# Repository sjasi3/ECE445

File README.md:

READ ME File so repo isnt empty

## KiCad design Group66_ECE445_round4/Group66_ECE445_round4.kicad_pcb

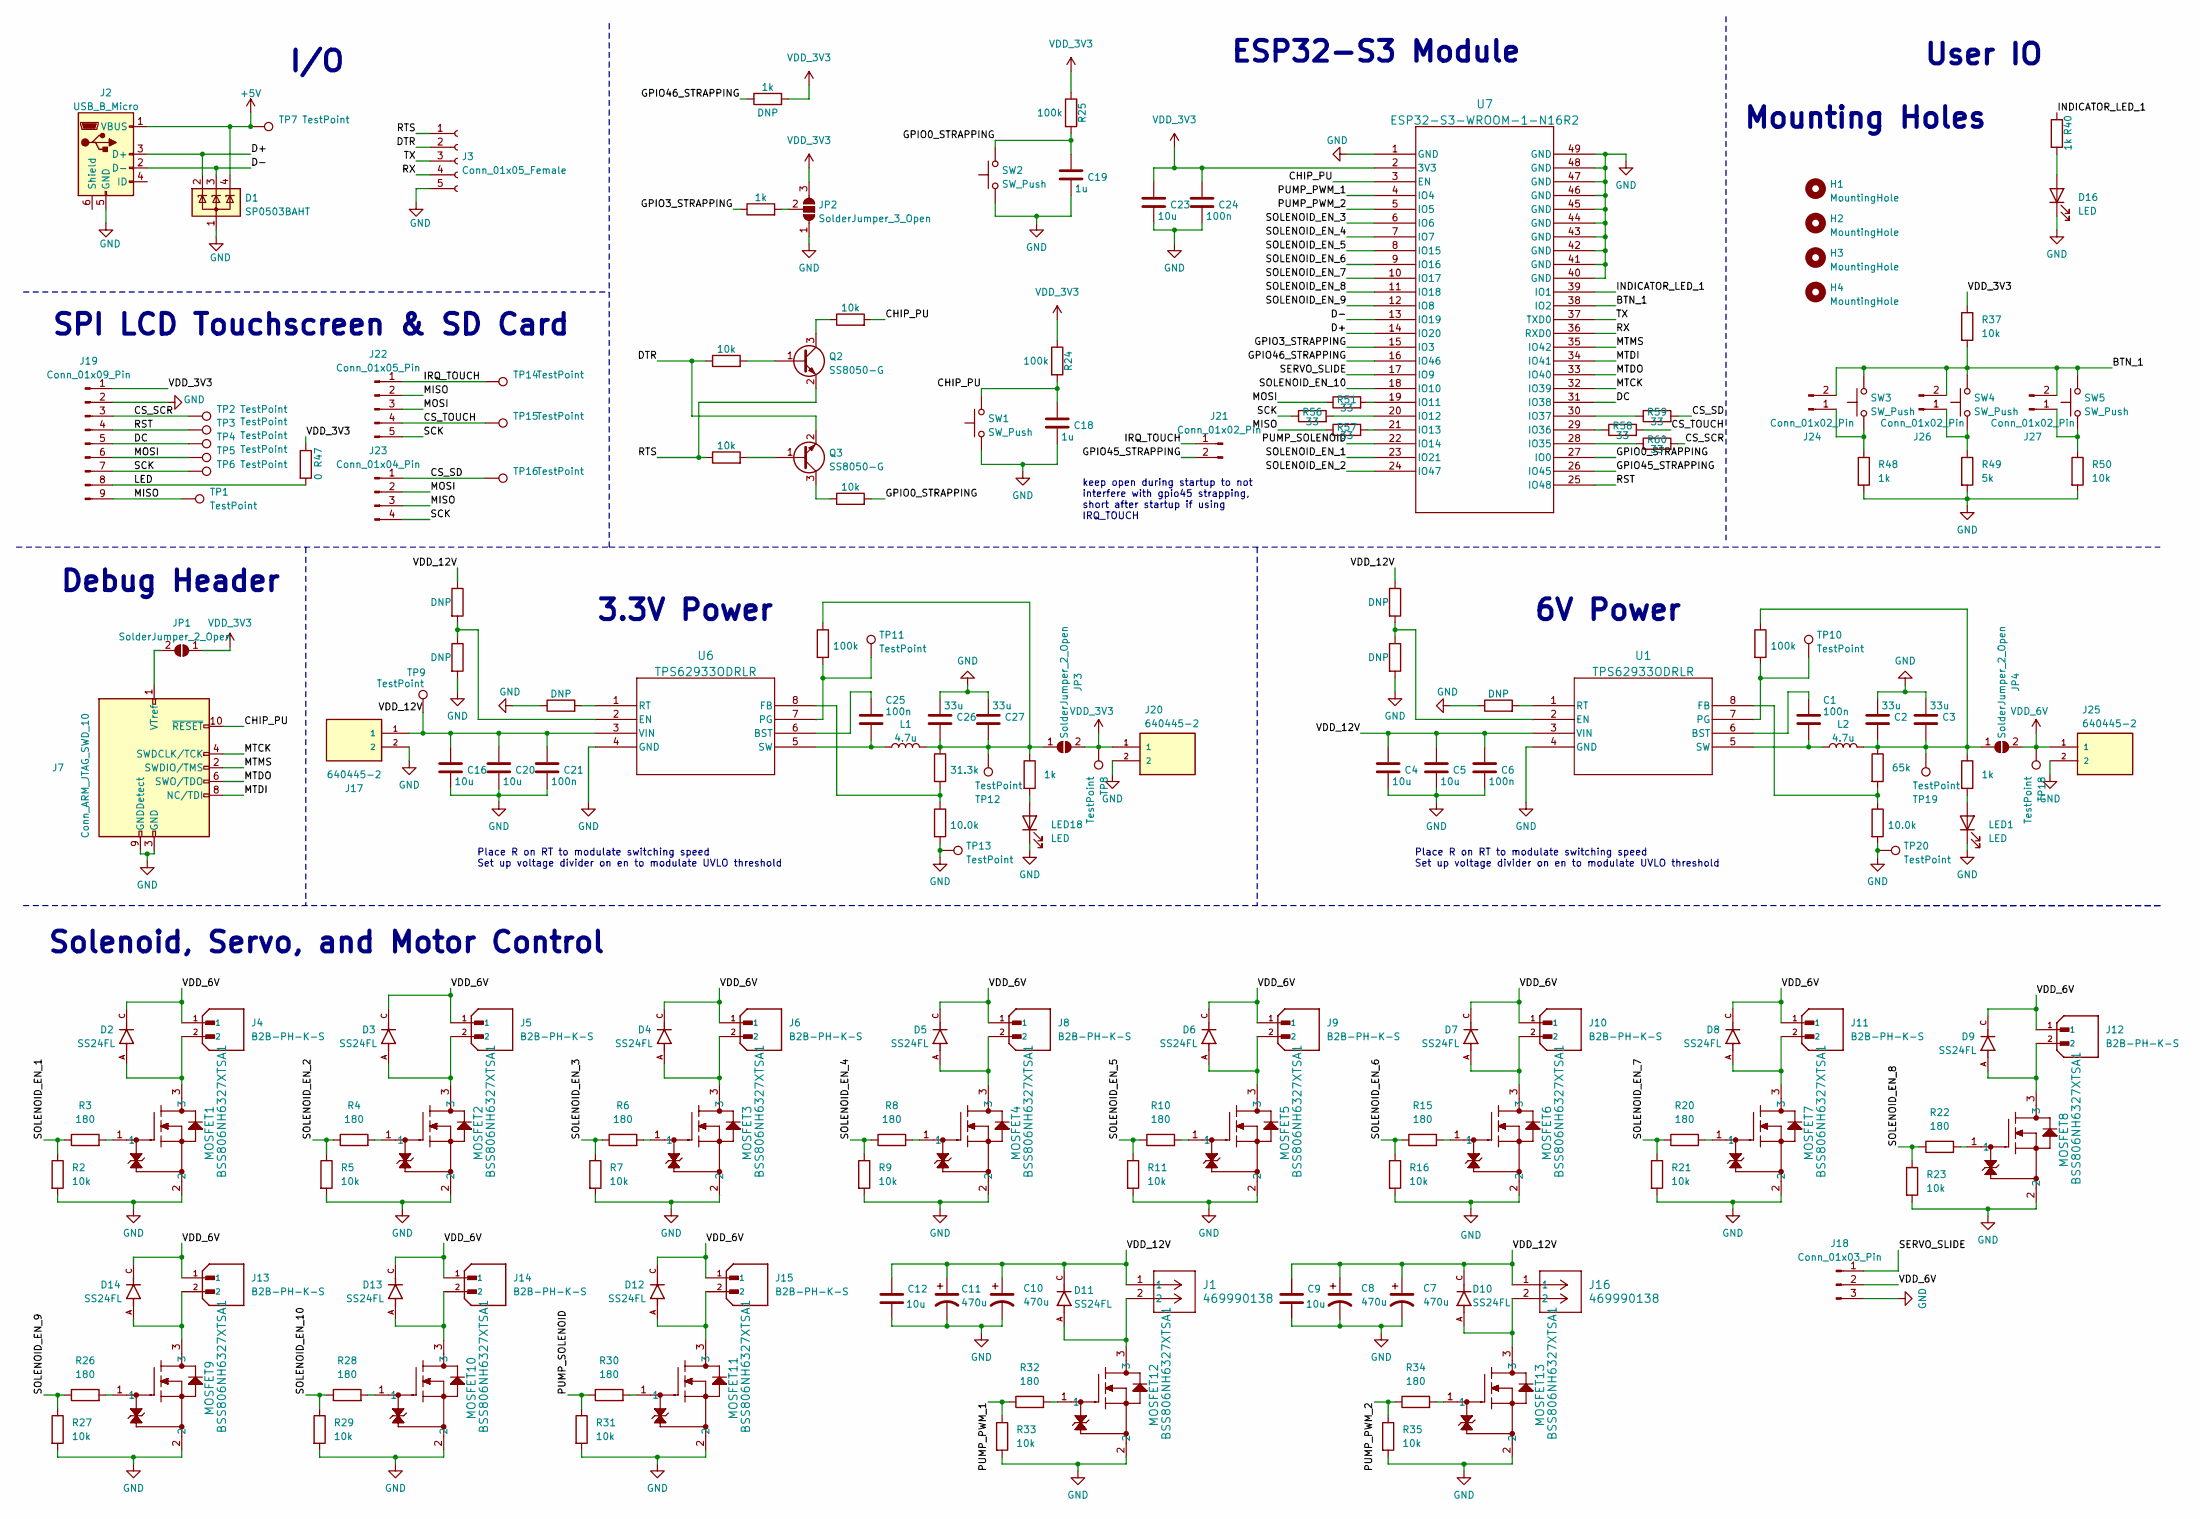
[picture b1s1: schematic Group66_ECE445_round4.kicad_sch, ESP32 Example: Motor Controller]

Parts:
C1, C6, C21, C24, C25: 100n; C_0805_2012Metric_Pad1.18x1.45mm_HandSolder
C2, C3, C26, C27: 33u; C_0805_2012Metric_Pad1.18x1.45mm_HandSolder
C4, C5, C9, C12, C16, C20, C23: 10u; C_0805_2012Metric_Pad1.18x1.45mm_HandSolder
C7, C8, C10, C11: 470u; CP_Radial_D8.0mm_P5.00mm
C18, C19: 1u; C_0805_2012Metric_Pad1.18x1.45mm_HandSolder
D1: SP0503BAHT; SOT-143
D2, D3, D4, D5, D6, D7, D8, D9, D10, D11, D12, D13, D14: SS24FL; SODFL3617X108N; PARTREV A
D16: LED; LED_0805_2012Metric_Pad1.15x1.40mm_HandSolder
H1, H2, H3, H4: MountingHole; MountingHole_3.2mm_M3
J1, J16: 469990138; CONN_SD-5566-002_02_MOL
J2: USB_B_Micro; USB_Micro-B_Amphenol_10118194_Horizontal
J3: Conn_01x05_Female; PinHeader_1x05_P2.54mm_Vertical
J4, J5, J6, J8, J9, J10, J11, J12, J13, J14, J15: B2B-PH-K-S; JST_B2B-PH-K-S; PARTREV N/A
J7: Conn_ARM_JTAG_SWD_10; IDC-Header_2x05_P2.54mm_Vertical
J17, J20, J25: 640445-2; TE_640445-2; PARTREV R
J18: Conn_01x03_Pin; PinHeader_1x03_P2.54mm_Vertical
J19: Conn_01x09_Pin; PinHeader_1x09_P2.54mm_Vertical
J21, J24, J26, J27: Conn_01x02_Pin; PinHeader_1x02_P2.54mm_Vertical
J22: Conn_01x05_Pin; PinHeader_1x05_P2.54mm_Vertical
J23: Conn_01x04_Pin; PinHeader_1x04_P2.54mm_Vertical
JP1, JP3, JP4: SolderJumper_2_Open; SolderJumper-2_P1.3mm_Open_TrianglePad1.0x1.5mm
JP2: SolderJumper_3_Open; SolderJumper-3_P2.0mm_Open_TrianglePad1.0x1.5mm
L1, L2: 4.7u; L_Taiyo-Yuden_NR-60xx
LED1, LED18: LED; LED_0805_2012Metric_Pad1.15x1.40mm_HandSolder
MOSFET1, MOSFET2, MOSFET3, MOSFET4, MOSFET5, MOSFET6, MOSFET7, MOSFET8, MOSFET9, MOSFET10, MOSFET11, MOSFET12, MOSFET13: BSS806NH6327XTSA1; SOT23_BSS806NH6327XTSA1_INF
Q2, Q3: SS8050-G; SOT-23
R1, R38, R41, R42, R43, R52: DNP; R_0805_2012Metric_Pad1.20x1.40mm_HandSolder
R2, R5, R7, R9, R11, R13, R14, R16, R18, R19, R21, R23, R27, R29, R31, R33, R35, R37, R50: 10k; R_0805_2012Metric_Pad1.20x1.40mm_HandSolder
R3, R4, R6, R8, R10, R15, R20, R22, R26, R28, R30, R32, R34: 180; R_0805_2012Metric_Pad1.20x1.40mm_HandSolder
R12, R17, R40, R46, R48, R54: 1k; R_0805_2012Metric_Pad1.20x1.40mm_HandSolder
R24, R25, R36, R39: 100k; R_0805_2012Metric_Pad1.20x1.40mm_HandSolder
R44: 31.3k; R_0805_2012Metric_Pad1.20x1.40mm_HandSolder
R45, R55: 10.0k; R_0805_2012Metric_Pad1.20x1.40mm_HandSolder
R47: 0; R_0805_2012Metric_Pad1.20x1.40mm_HandSolder
R49: 5k; R_0805_2012Metric_Pad1.20x1.40mm_HandSolder
R51, R56, R57, R58, R59, R60: 33; R_0805_2012Metric_Pad1.20x1.40mm_HandSolder
R53: 65k; R_0805_2012Metric_Pad1.20x1.40mm_HandSolder
SW1, SW2, SW3, SW4, SW5: SW_Push; SW_SPST_B3S-1000
TP1, TP2, TP3, TP4, TP5, TP6, TP7, TP8, TP9, TP10, TP11, TP12, TP13, TP14, TP15, TP16, TP18, TP19, TP20: TestPoint; TestPoint_Pad_D1.5mm
U1, U6: TPS62933ODRLR; SOT5X3-8_DRL_TEX
U7: ESP32-S3-WROOM-1-N16R2; ESP32-S3-WROOM-1_EXP

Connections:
+5V: D1.4 (K), J2.1 (VBUS), TP7.1
/BTN_1: J24.2, J26.2, J27.2, R37.2, SW3.2, SW4.2, SW5.2, U7.38 (IO2)
/CHIP_PU: C18.1, J7.10 (~RESET), R18.2, R24.2, SW1.2, U7.3 (EN)
/CS_SCR: J19.3, R60.2, TP2.1
/CS_SD: J23.1, R59.2, TP16.1
/CS_TOUCH: J22.4, R58.2, TP15.1
/D+: D1.2 (K), J2.3 (D+), U7.14 (IO20)
/D-: D1.3 (K), J2.2 (D-), U7.13 (IO19)
/DC: J19.5, TP4.1, U7.31 (IO38)
/DTR: J3.2, Q3.2 (E), R13.1
/GPIO0_STRAPPING: C19.1, R19.2, R25.2, SW2.2, U7.27 (IO0)
/GPIO3_STRAPPING: R17.1, U7.15 (IO3)
/GPIO45_STRAPPING: J21.2, U7.26 (IO45)
/GPIO46_STRAPPING: R12.1, U7.16 (IO46)
/INDICATOR_LED_1: R40.1, U7.39 (IO1)
/IRQ_TOUCH: J21.1, J22.1, TP14.1
/LED: J19.8, R47.2
/MISO: J19.9, J22.2, J23.3, R57.1, TP1.1
/MOSI: J19.6, J22.3, J23.2, R51.1, TP5.1
/MTCK: J7.4 (SWDCLK/TCK), U7.32 (IO39)
/MTDI: J7.8 (NC/TDI), U7.34 (IO41)
/MTDO: J7.6 (SWO/TDO), U7.33 (IO40)
/MTMS: J7.2 (SWDIO/TMS), U7.35 (IO42)
/PUMP_PWM_1: R32.1, R33.1, U7.4 (IO4)
/PUMP_PWM_2: R34.1, R35.1, U7.5 (IO5)
/PUMP_SOLENOID: R30.1, R31.1, U7.22 (IO14)
/RST: J19.4, TP3.1, U7.25 (IO48)
/RTS: J3.1, Q2.2 (E), R14.1
/RX: J3.4, U7.36 (RXD0)
/SCK: J19.7, J22.5, J23.4, R56.1, TP6.1
/SERVO_SLIDE: J18.1, U7.17 (IO9)
/SOLENOID_EN_1: R2.1, R3.1, U7.23 (IO21)
/SOLENOID_EN_2: R4.1, R5.1, U7.24 (IO47)
/SOLENOID_EN_3: R6.1, R7.1, U7.6 (IO6)
/SOLENOID_EN_4: R8.1, R9.1, U7.7 (IO7)
/SOLENOID_EN_5: R10.1, R11.1, U7.8 (IO15)
/SOLENOID_EN_6: R15.1, R16.1, U7.9 (IO16)
/SOLENOID_EN_7: R20.1, R21.1, U7.10 (IO17)
/SOLENOID_EN_8: R22.1, R23.1, U7.11 (IO18)
/SOLENOID_EN_9: R26.1, R27.1, U7.12 (IO8)
/SOLENOID_EN_10: R28.1, R29.1, U7.18 (IO10)
/TX: J3.3, U7.37 (TXD0)
/VDD_12V: C4.1, C5.1, C6.1, C7.1, C8.1, C9.1, C10.1, C11.1, C12.1, C16.1, C20.1, C21.1, D10.C, D11.C, J1.1, J16.1, J17.1, R1.1, R38.1, TP9.1, U1.3 (VIN), U6.3 (VIN)
GND: C2.2, C3.2, C4.2, C5.2, C6.2, C7.2, C8.2, C9.2, C10.2, C11.2, C12.2, C16.2, C18.2, C19.2, C20.2, C21.2, C23.2, C24.2, C26.2, C27.2, D1.1 (A), D16.1 (K), J2.5 (GND), J3.5, J7.3 (GND), J7.5 (GND), J7.9 (GNDDetect), J17.2, J18.3, J19.2, J20.2, J25.2, JP2.1 (A), LED1.1 (K), LED18.1 (K), MOSFET1.2, MOSFET2.2, MOSFET3.2, MOSFET4.2, MOSFET5.2, MOSFET6.2, MOSFET7.2, MOSFET8.2, MOSFET9.2, MOSFET10.2, MOSFET11.2, MOSFET12.2, MOSFET13.2, R2.2, R5.2, R7.2, R9.2, R11.2, R16.2, R21.2, R23.2, R27.2, R29.2, R31.2, R33.2, R35.2, R41.2, R42.2, R43.1, R45.2, R48.2, R49.2, R50.2, R52.1, R55.2, SW1.1, SW2.1, TP13.1, TP20.1, U1.4 (GND), U6.4 (GND), U7.1 (GND), U7.40 (GND), U7.41 (GND), U7.42 (GND), U7.43 (GND), U7.44 (GND), U7.45 (GND), U7.46 (GND), U7.47 (GND), U7.48 (GND), U7.49 (GND)
unnamed: D2.A, J4.2, MOSFET1.3
unnamed: D3.A, J5.2, MOSFET2.3
unnamed: D4.A, J6.2, MOSFET3.3
unnamed: D5.A, J8.2, MOSFET4.3
unnamed: D6.A, J9.2, MOSFET5.3
unnamed: D7.A, J10.2, MOSFET6.3
unnamed: D8.A, J11.2, MOSFET7.3
unnamed: D9.A, J12.2, MOSFET8.3
unnamed: D10.A, J16.2, MOSFET13.3
unnamed: D11.A, J1.2, MOSFET12.3
unnamed: D12.A, J15.2, MOSFET11.3
unnamed: D13.A, J14.2, MOSFET10.3
unnamed: D14.A, J13.2, MOSFET9.3
unnamed: D16.2 (A), R40.2
unnamed: J7.1 (VTref), JP1.2 (B)
unnamed: J24.1, R48.1, SW3.1
unnamed: J26.1, R49.1, SW4.1
unnamed: J27.1, R50.1, SW5.1
unnamed: JP2.2 (C), R17.2
unnamed: C26.1, C27.1, JP3.1 (A), L1.2, R36.1, R44.1, R46.1, TP12.1
unnamed: C2.1, C3.1, JP4.1 (A), L2.2, R39.1, R53.1, R54.1, TP19.1
unnamed: LED1.2 (A), R54.2
unnamed: LED18.2 (A), R46.2
unnamed: MOSFET1.1, R3.2
unnamed: MOSFET2.1, R4.2
unnamed: MOSFET3.1, R6.2
unnamed: MOSFET4.1, R8.2
unnamed: MOSFET5.1, R10.2
unnamed: MOSFET6.1, R15.2
unnamed: MOSFET7.1, R20.2
unnamed: MOSFET8.1, R22.2
unnamed: MOSFET9.1, R26.2
unnamed: MOSFET10.1, R28.2
unnamed: MOSFET11.1, R30.2
unnamed: MOSFET12.1, R32.2
unnamed: MOSFET13.1, R34.2
unnamed: Q2.1 (B), R13.2
unnamed: Q2.3 (C), R18.1
unnamed: Q3.1 (B), R14.2
unnamed: Q3.3 (C), R19.1
unnamed: C1.1, U1.6 (BST)
unnamed: R38.2, R41.1, U1.2 (EN)
unnamed: R53.2, R55.1, U1.8 (FB)
unnamed: R39.2, TP10.1, U1.7 (PG)
unnamed: R52.2, U1.1 (RT)
unnamed: C1.2, L2.1, U1.5 (SW)
unnamed: C25.1, U6.6 (BST)
unnamed: R1.2, R42.1, U6.2 (EN)
unnamed: R44.2, R45.1, U6.8 (FB)
unnamed: R36.2, TP11.1, U6.7 (PG)
unnamed: R43.2, U6.1 (RT)
unnamed: C25.2, L1.1, U6.5 (SW)
unnamed: R51.2, U7.19 (IO11)
unnamed: R56.2, U7.20 (IO12)
unnamed: R57.2, U7.21 (IO13)
unnamed: R60.1, U7.28 (IO35)
unnamed: R58.1, U7.29 (IO36)
unnamed: R59.1, U7.30 (IO37)
VDD_3V3: C23.1, C24.1, J19.1, J20.1, JP1.1 (A), JP2.3 (B), JP3.2 (B), R12.2, R24.1, R25.1, R37.1, R47.1, TP8.1, U7.2 (3V3)
VDD_6V: D2.C, D3.C, D4.C, D5.C, D6.C, D7.C, D8.C, D9.C, D12.C, D13.C, D14.C, J4.1, J5.1, J6.1, J8.1, J9.1, J10.1, J11.1, J12.1, J13.1, J14.1, J15.1, J18.2, J25.1, JP4.2 (B), TP18.1

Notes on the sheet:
keep open during startup to not interfere with gpio45 strapping, short after startup if using IRQ_TOUCH
Place R on RT to modulate switching speed Set up voltage divider on en to modulate UVLO threshold
ESP32-S3 Module
Solenoid, Servo, and Motor Control
6V Power
User IO
Debug Header
Mounting Holes
3.3V Power
SPI LCD Touchscreen & SD Card
I/O

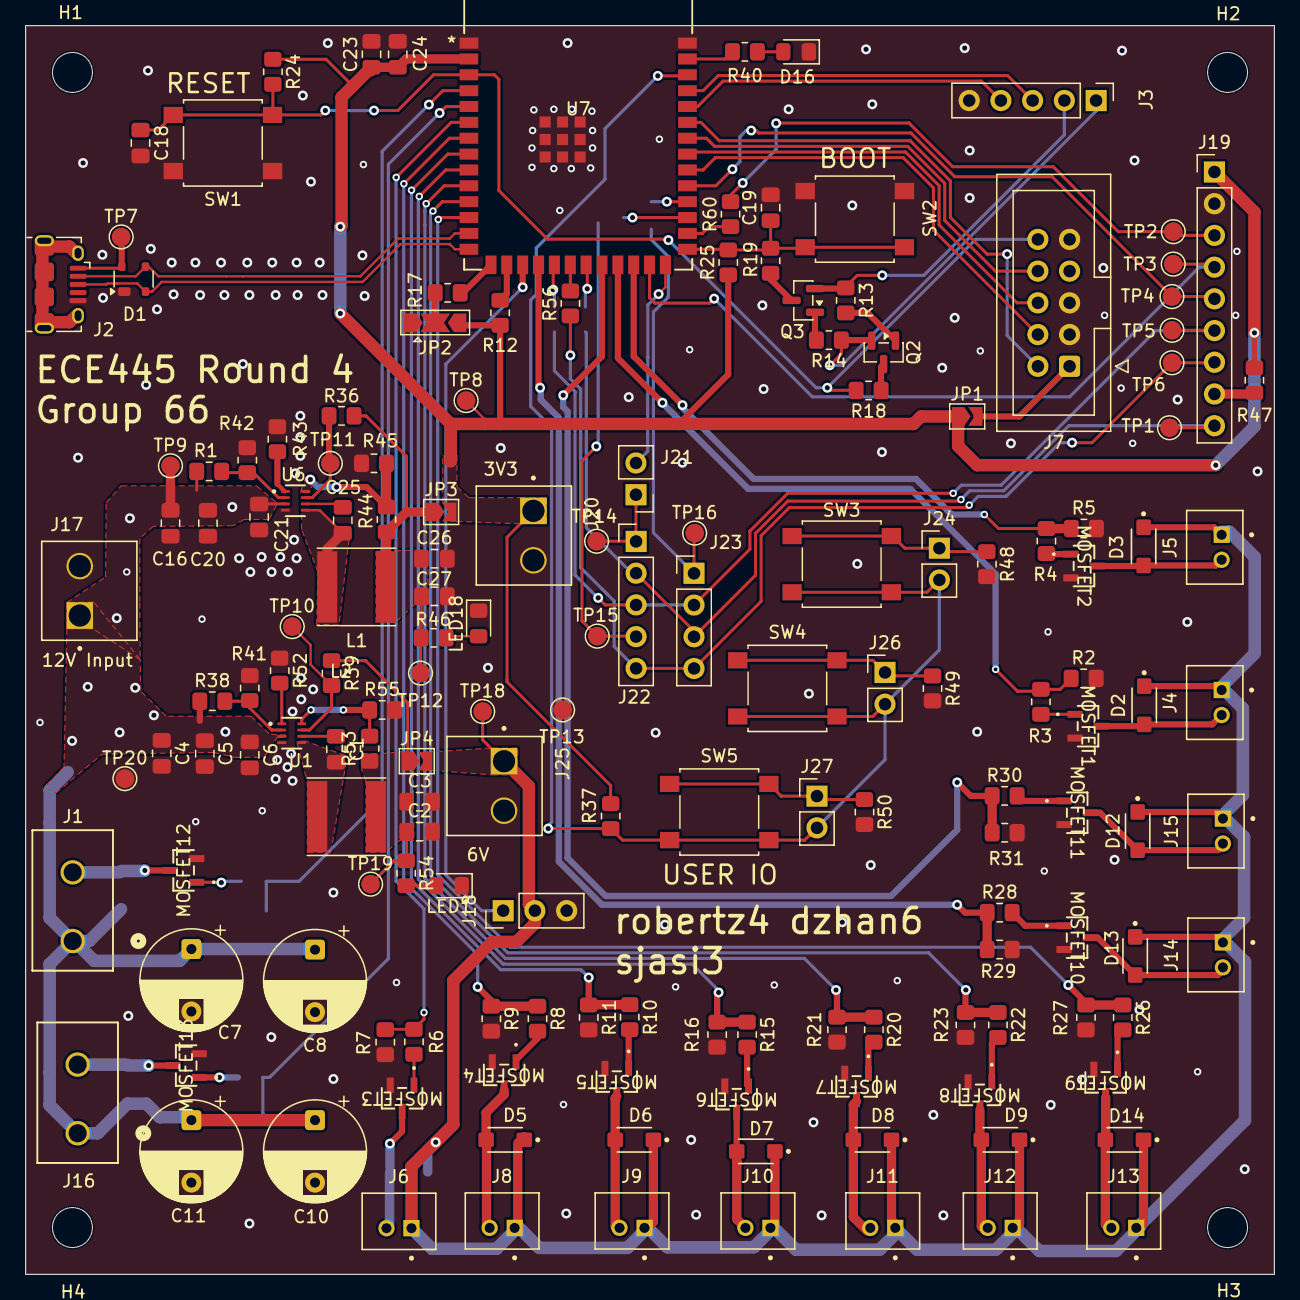
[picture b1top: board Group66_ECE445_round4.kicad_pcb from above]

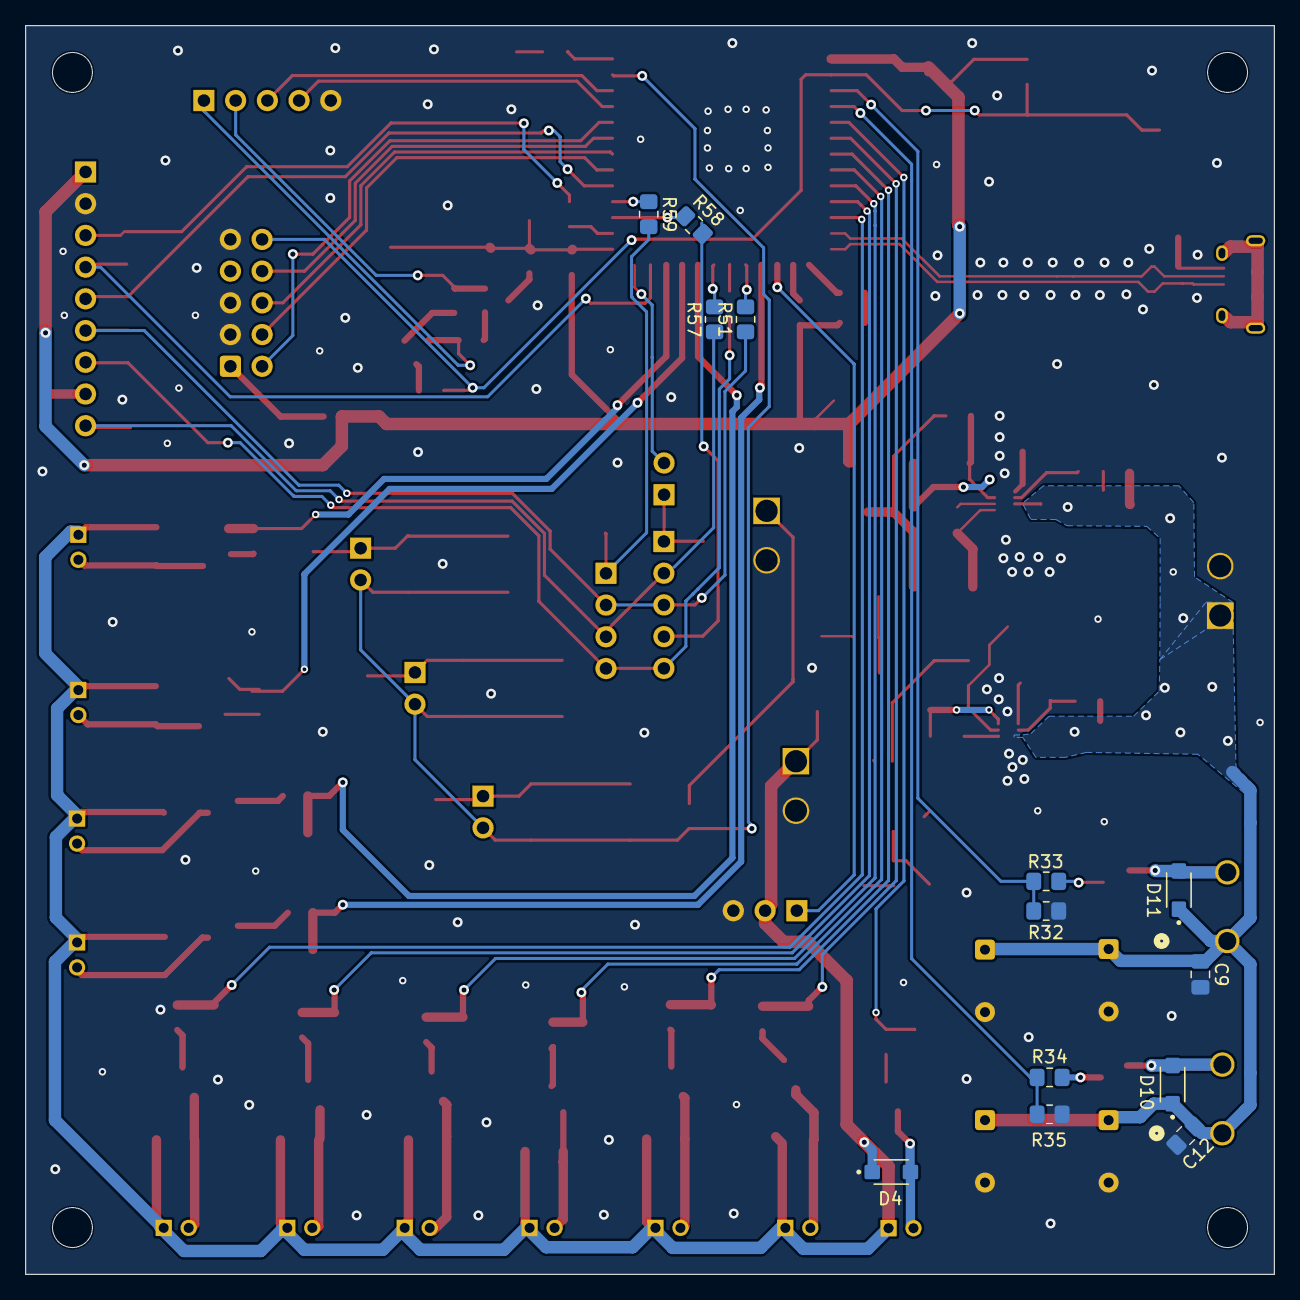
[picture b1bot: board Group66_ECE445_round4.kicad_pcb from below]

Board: 2 copper layers, 100.0 x 100.0 mm, 178 parts (13 on the bottom side), 104 nets.

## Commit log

2026-02-24 First commit for README in main
2026-02-26 PCB round 1 design
    Schematic done, layout not done
2026-02-26 Added first revision of routed PCB layout
2026-02-26 Create Log
2026-02-26 Created notebook directories
2026-02-26 Log updates
2026-02-26 added dir
2026-02-26 PCB round 1
    Finished layout
2026-02-28 Create 2_26 Notebook Entry
2026-03-01 Update 2_26 Notebook Entry
2026-03-04 Made changes toward round two PCB Design
    Schematic done, Layout not done.
    Changed 5V input to 6V input
    Removed previous user IO and added SD card and touchscreen functionality
2026-03-05 Made changes toward round two PCB Design
    Schematic done, Layout done but has some DRC errors.
    Changed 5V input to 6V input
    Removed some of previous user IO and added SD card and touchscreen functionality
    One button and one LED indicator still remain from previous IO
2026-03-05 Revised Robert's round 2 PCB board
    Fixed clearance issues, connected unconnected nets. For footprints that inherently had a clearance issues, I ignored DRC clearance check.
2026-03-05 Layout tweaks
    Fixed fills and some DRC errors, cleaned up layout
2026-03-05 Layout tweaks
    Added some stitching vias, updated VDD_6V fill
2026-03-05 Upload for match
2026-03-05 Create subdir
2026-03-05 Got wireless code button to function
2026-03-05 3/5/2025 PCB round 2
    New notebook entry for 3/5/2025 detailing changes made to PCB design for round 2
2026-03-05 Update Log
2026-03-05 current curve from solenoid testing
2026-03-09 Created cad files for breadboard demo
    to be 3d printed
2026-03-09 Create read
2026-03-09 STL file upload
2026-03-09 Updated harmonica main frame
2026-03-09 STL file for harmonica frame v2
2026-03-09 thickened nozzles so that they can 3D print
2026-03-10 Updated notebook
2026-03-12 Round 3 PCB files
2026-03-12 Create Notebook entry
2026-03-12 Update Notebook entry
2026-03-12 Add figure for engineering notebook entry
2026-03-12 Create Engineering notebook entry
2026-03-12 Update Engineering notebook entry
2026-03-12 Rename 3_12 Figure 4 PCB round 3 Schematic.pdf to 3_12 Figure 6 PCB round 3 Schematic.pdf
2026-03-23 Created a test html-only midi parser
    This code can be pasted into the html portion of the esp32 code. It successfully parses midi files and plays notes, giving values for h = hole number, a = 0 for blow, h = 0/1/2 for nothing/blow/suck,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
2026-03-26 Round 4 PCB design
2026-03-29 Create Notebook entry
    notebook entry for round 4 pcb design 3/26
2026-03-29 Rename notebooks/robertz4/3_5 PCB round 2 to notebooks/robertz4/3_5 PCB Round 2/Notebook entry
2026-03-30 Remade solenoid holders for 5 solenoids
    Made a two-layer offset solenoid holder. This should be able to hold all 10 solenoids.
2026-03-31 Renamed files to clear confusion
2026-04-23 Code
2026-04-27 updated parser to include PWM
    parses midi for pwm from -100 to 100
2026-04-27 parser with offline and testing GUI
2026-04-27 I think thats everything
2026-04-27 ok now thats everything
2026-05-07 Uploaded final version of the HTML midi parser
    I never got around to actually uploading the final version of the HTMl midi parser. I added manual controls and changed the color scheme by a bit.
2026-05-07 Uploaded files
    Uploaded solenoid air flow testing images from 4/27. Uploaded images of our 12V motor we got from Walmart (04/22). Uploaded air flow testing image for 4.5V DC motor (03.09). Uploaded motor ripple ima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
2026-05-07 Updated Log
2026-05-07 Reuploaded images.
    Uploaded solenoid air flow testing images from 4/27. Uploaded images of our 12V motor we got from Walmart (04/22). Uploaded air flow testing image for 4.5V DC motor (03.09).
2026-05-07 added some more details and dates
2026-05-07 added code
